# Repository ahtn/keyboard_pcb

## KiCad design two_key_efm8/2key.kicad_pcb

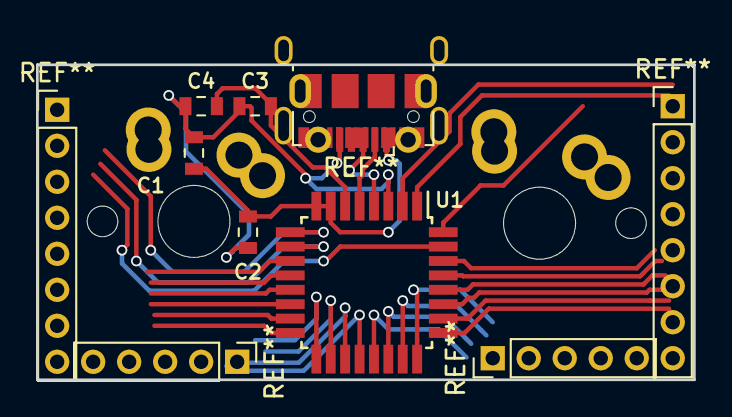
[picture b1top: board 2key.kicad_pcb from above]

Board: 2 copper layers, 36.5 x 17.5 mm, 8 parts (0 on the bottom side), 5 nets.

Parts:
C1, C2, C3, C4: C; C_0603_1608Metric
J1: USB_OTG; USB_Micro-B_Molex-105017-0001
K1_1, K1_1#2: SW_PUSH; Cherry_MX_Matias_No_Silk_Border
U1: EFM8UB2_32; TQFP-32_7x7mm_P0.8mm

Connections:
+3V3: C3.1, C4.1, U1.6
GND: C1.2, C2.2, C3.2, C4.2, J1.5, U1.3
unnamed: C1.1, C2.1, J1.1, U1.7, U1.8
unnamed: J1.2, U1.5
unnamed: J1.3, U1.4

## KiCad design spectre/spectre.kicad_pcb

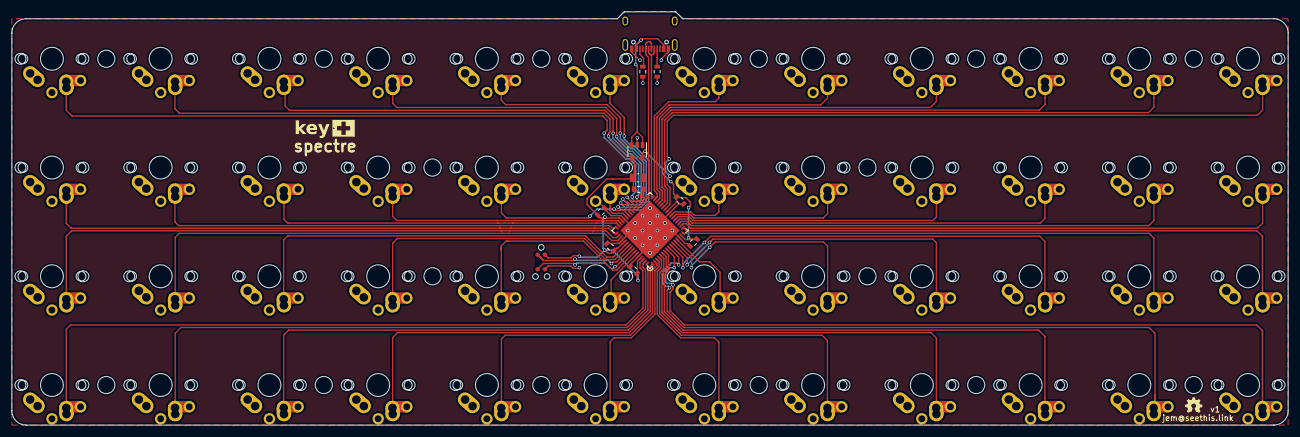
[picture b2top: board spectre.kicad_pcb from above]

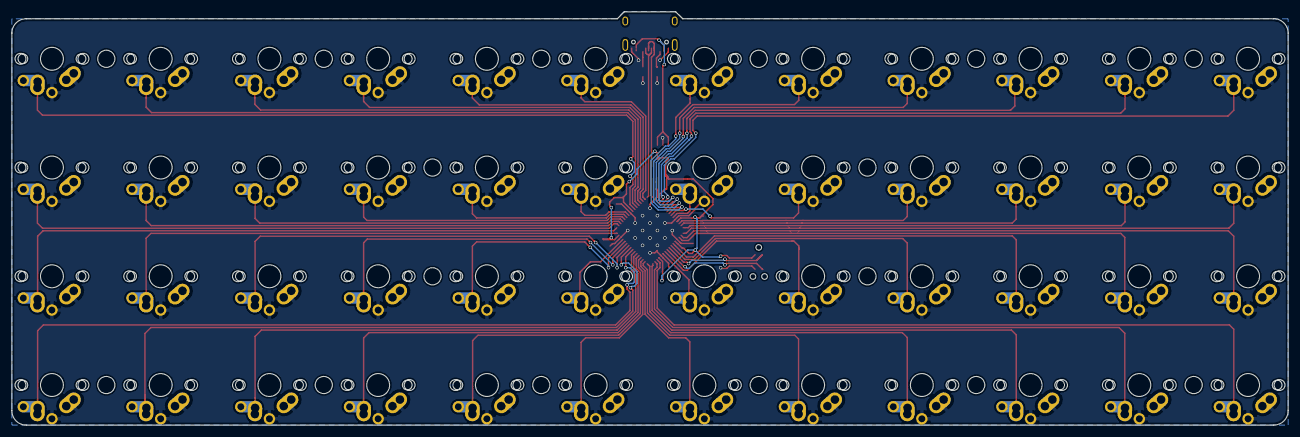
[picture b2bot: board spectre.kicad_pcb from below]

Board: 2 copper layers, 223.0 x 72.2 mm, 61 parts (48 on the bottom side), 57 nets.

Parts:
C1: 10uF; C_0805_2012Metric
C2, C3, C4, C5, C6, C7: 0.1uF; C_0603_1608Metric
J1: TC2030-IDC; TC2030-NL_SMALL
J2: USB_Type_C_2.0_Receptacle; USB_TypeC_U31F-24SNA0201
K0, K1, K2, K3, K4, K5, K6, K7, K8, K9, K10, K11, K12, K13, K14, K15, K16, K17, K18, K19, K20, K21, K22, K23, K24, K25, K26, K27, K28, K29, K30, K31, K32, K33, K34, K35, K36, K37, K38, K39, K40, K41, K42, K43, K44, K45, K46, K47: K00; Cherry_MX_Matias_KailhLP_NoSilk
R1, R2: R; R_0603_1608Metric
U1: MIC550X; SOT-23-5
U2: ATXMEGA64A3U-MH; QFN-64-1EP_9x9mm_P0.5mm

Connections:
+5V: J2.A4, J2.B4, U1.1, U1.3
/D+: J2.A6, J2.B6, U2.33
/D-: J2.A7, J2.B7, U2.32
/KEY0: K0.2, U2.37
/KEY1: K1.2, U2.36
/KEY2: K2.2, U2.38
/KEY3: K3.2, U2.39
/KEY4: K4.2, U2.40
/KEY5: K5.2, U2.41
/KEY6: K6.2, U2.31
/KEY7: K7.2, U2.30
/KEY8: K8.2, U2.29
/KEY9: K9.2, U2.28
/KEY10: K10.2, U2.27
/KEY11: K11.2, U2.26
/KEY12: K12.2, U2.49
/KEY13: K13.2, U2.48
/KEY14: K14.2, U2.47
/KEY15: K15.2, U2.46
/KEY16: K16.2, U2.42
/KEY17: K17.2, U2.43
/KEY18: K18.2, U2.23
/KEY19: K19.2, U2.22
/KEY20: K20.2, U2.21
/KEY21: K21.2, U2.20
/KEY22: K22.2, U2.19
/KEY23: K23.2, U2.18
/KEY24: K24.2, U2.50
/KEY25: K25.2, U2.51
/KEY26: K26.2, U2.54
/KEY27: K27.2, U2.55
/KEY28: K28.2, U2.58
/KEY29: K29.2, U2.59
/KEY30: K30.2, U2.13
/KEY31: K31.2, U2.12
/KEY32: K32.2, U2.11
/KEY33: K33.2, U2.10
/KEY34: K34.2, U2.16
/KEY35: K35.2, U2.17
/KEY36: K36.2, U2.62
/KEY37: K37.2, U2.63
/KEY38: K38.2, U2.64
/KEY39: K39.2, U2.1
/KEY40: K40.2, U2.2
/KEY41: K41.2, U2.3
/KEY42: K42.2, U2.4
/KEY43: K43.2, U2.5
/KEY44: K44.2, U2.6
/KEY45: K45.2, U2.7
/KEY46: K46.2, U2.9
/KEY47: K47.2, U2.8
/PDI: J1.1, U2.56
/RST: J1.5, U2.57
GND: C1.1, C2.1, C3.1, C4.1, C5.1, C6.1, C7.1, J1.6, J2.A1, J2.B1, K0.1, K1.1, K2.1, K3.1, K4.1, K5.1, K6.1, K7.1, K8.1, K9.1, K10.1, K11.1, K12.1, K13.1, K14.1, K15.1, K16.1, K17.1, K18.1, K19.1, K20.1, K21.1, K22.1, K23.1, K24.1, K25.1, K26.1, K27.1, K28.1, K29.1, K30.1, K31.1, K32.1, K33.1, K34.1, K35.1, K36.1, K37.1, K38.1, K39.1, K40.1, K41.1, K42.1, K43.1, K44.1, K45.1, K46.1, K47.1, R1.2, R2.2, U1.2, U2.14, U2.24, U2.34, U2.44, U2.52, U2.60, U2.65
unnamed: J2.A5, R2.1
unnamed: J2.B5, R1.1
VCC: C1.2, C2.2, C3.2, C4.2, C5.2, C6.2, C7.2, J1.2, U1.4, U1.5, U2.15, U2.25, U2.35, U2.45, U2.53, U2.61

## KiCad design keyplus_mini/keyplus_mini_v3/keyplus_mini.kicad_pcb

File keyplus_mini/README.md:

# keyplus mini beta

## Errata rev2

The SS and MO pins are mislabeled. The SS pin should be MO, and the MO pin
should be SS.

## Wiring

### Wiring key matrix

The key matrix should be wired to the ROW and COL pins on the PCB. Wiring of the
ROW and COL pins should start from the lowest number pin (i.e. `ROW0`
and `COL0`) and work up in consecutive order. The diodes in the key matrix should
point from the COL to ROW pins (other scan modes not implemented yet).

The `COL15, COL14, COL13, COL12` pins (underlined on the PCB) may also be used
as `ROW` pins. They map to the following row pins:

* ROW6: COL15
* ROW7: COL14
* ROW8: COL13
* ROW9: COL12

Thus it is possible to have up to 120 keys connected using a 10x12 matrix.

### Wired split with I2C

To connect to boards with I2C for wired split, connect the 5V, SDA, SCL, and
GND pins between devices. You can connect several devices in this manner. They
just need to share 5V, SDA, SCL and GND pins.

I would recommend **NOT** using TRRS connectors for wired split. While
connecting and disconnecting the cabel, the contacts inside the TRRS cable can
short to one another. Instead, I would recommend using micro USB ports, or
another connector that doesn't short it's contacts when it is
plugged/unplugged. Then you will be able to take advantage of the
wireless/wired hot plugging functionality without worrying about damaging the
hardware.  You can find male-to-male micro USB cables online with a bit of
searching.

### Wireless with nRF24L01+

To use wireless mode, you will need a battery and a nRF24L01+ module. The
battery should be 3V. Some options for the battery are 1xCR2032, 2xAA/AAA, or
1xAA/AAA with a boost converter. Note the keyplus mini controller does not
support any sort of charging of the batteries. When there is no USB connecting
the device will run off battery power. When the USB is plugged in, it will
automatically switch to run off USB power. To connect the battery connect:

* BAT -> positive battery terminal
* GND -> negative battery terminal

To connect an nRF24L01+ module you will need to connect these pins:

* xmega -> nRF24L01+
* R0 -> CE
* R1  -> IRQ
* MO -> MO / MOSI  (Note: rev2 PCB use SS instead)
* MI -> MI / MISO
* SS -> SS / CSN (Note: rev2 PCB use MO instead)
* SCK -> SCK
* GND -> GND
* 3V -> 3.3V

Note: currently the IRQ pin is not used in the code, but I'll add code to take advantage of it soon.

### PCB schematic for rev 2

[Schematic for keyplus mini](https://rawgit.com/ahtn/keyboard_pcb/bb20b354216aa1858254db9946aa67aa8df67bfd/keyplus_mini/rev2/keyplus_mini.pdf)

### Mechanical information for rev 2

## Layout file format and programming

TODO

For [prebuilt versions of the loader and firmware](https://github.com/ahtn/keyplus/releases).

For the mean time, refer to the
[example layouts](https://github.com/ahtn/keyplus/tree/master/layouts), and the
[list of available keycodes](https://github.com/ahtn/keyplus/blob/master/host-software/layout/mapped_keycodes.py#L8).

## Current firmware limitations

Firmware is still in beta and several features are not completely
finished yet. Some prominent ones:

* Macro and hold keycodes can't be used in the layout config file yet.
* No LED support yet (including indicators)
* Pairing Unifying mouse is not exposed to devices yet

## Testing key matrix

The firmware supports a mode where it will pass the raw keyboard matrix data to
the PC. This can be used to check the row and column pairs in your key matrix.
Currently, this can only be used on the command line using a python script
[`keyplus/host-software/keyplus_cli.py`](https://github.com/ahtn/keyplus/blob/master/host-software/keyplus_cli.py).

To use the keyboard matrix passthrough mode, run `./keyplus_cli.py passthrough`
and you should see output like this:

```
$$ ./keyplus_cli.py passthrough
r3c5

r3c0

r1c0

r0c1
r0c1 r1c1
r1c1
r1c1 r3c3
r3c3
```

Where each line shows which keys in the matrix are currently being pressed.
Note only devices directly connected by USB will report key presses using
passthrough mode.

## Unifying flasher

First working version of the Unifying flashing script can be
[found here](https://github.com/ahtn/keyplus/tree/master/host-software/uniflash).
Currently this script has only been tested on Linux.

There are two types of Unifying receivers that use different microcontrollers:
nRF24LU1+ and CC2544.
Only Unifying receivers that use the nRF24LU1+ are supported.

You can check which kind you have by looking at the firmware version number
of the receiver in Logitech's Unifying Software (or Solaar on Linux). If your
receiver has a firmware number that starts with 12 (e.g. `012.005.00028`), then
it uses the nRF24LU1+. If it starts with 24, then it uses the CC2544.

You can find Unifying receivers on aliexpress. I've tried a few different types
and they have all used the nRF24LU1+.

### How to add dongle to layout file

To be able to use the dongle, you need to add it to your layout file:

```yaml
devices:
  nrf_dongle:
    id: 7       # unique id that is not used by any of your other devices
    scan_mode: # rf dongle, so don't need a matrix
      mode: no_matrix # options: col_row, pins, no_matrix
```

Then you need to load the layout file and RF configuration file to the device.

## xusb bootloader

The bootloader installed on the ATxmega is the [xusb bootloader](https://github.com/ahtn/xusb-boot).
To enter bootloader mode press the reset button (or short the RST and GND
contacts) once when the USB cable is plugged in. The device will remain in
bootloader mode until it is programmed, or until the reset button is pressed a
second time.  For a more detailed explanation of the bootloader, [see
here](https://github.com/ahtn/xusb-boot#ways-to-enter-the-bootloader).

The lock bits on the ATxmega have been set to disable reading from flash by an
external programmer. This is done to protect the encryption keys that are
stored in flash.  Also, for security reasons the bootloader will wipe SRAM on
power up.

## Trouble shooting and known issues

* Make sure that the battery contacts have a firm connection. I've had issues
  sometimes with my homemade CR2032 holders where vibrations from typing would
  cause the contacts to be unreliable.
* When using the xmega+nRF24L01+ as the wireless receiver, it will sometimes
  drop packets [due to this issue](https://github.com/ahtn/keyplus/issues/3).
  Should be fixed soon. The nRF24LU1+ implementation doesn't have this problem.
* If you load broken firmware onto the xmega, it won't be visible to the GUI
  loader or flashing scripts. In this case you will need to enter it's bootloader
  manually by shorting the RST pin to GND while it is connected via USB. The
  bootloader is stored in a protected region of flash, so the bootloader should
  be unbrickable.
* Currently if you have multiple devices acting as wireless receivers at the
  same time, they will interfere with each other. This will be fixed later.

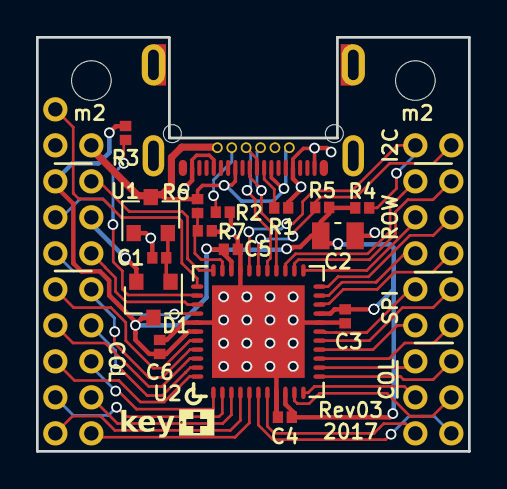
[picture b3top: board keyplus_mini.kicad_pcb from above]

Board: 2 copper layers, 24.0 x 23.0 mm, 20 parts (0 on the bottom side), 43 nets.

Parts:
C1: 1uF; C_0402_1005Metric
C2: 10uF; C_0805_2012Metric
C3, C4, C5, C6: 0.1uF; C_0402_1005Metric
D1: D_Schottky_x2_KCom_AAK; SOT-23
J1: USB_C_Receptacle; USB_TypeC_Hirose_CX70M-24P1
J2, J4: Conn_02x09_Odd_Even; PinHeader_2x09_P2.00mm_Vertical
J3: CONN_01X01; PinHeader_1x01_P2.00mm_Vertical
R1, R2: 5.1k; R_0402_1005Metric
R3, R4, R5: 10k; R_0402_1005Metric
R6, R7: 100k; R_0402_1005Metric
U1: MCP1700-3302E_SOT23; SOT-23
U2: ATXMEGA-A4U-EPAD; QFN-44-1EP_7x7mm_Pitch0.5mm

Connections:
+3V3: C2.2, C3.2, C4.2, C5.2, C6.2, D1.3, J2.3, R3.1, R4.1, R5.1, U2.9, U2.19, U2.31, U2.39
+5V: J1.A4, J1.A9, J1.B4, J1.B9, J2.2, R6.1, U1.3
+BATT: D1.2, J2.6
/D+: J1.A6, J1.B6, U2.27
/D-: J1.A7, J1.B7, U2.26
/PA0: J2.9, U2.40
/PA1: J2.10, U2.41
/PA2: J2.11, U2.42
/PA3: J2.12, U2.43
/PA4: J2.13, U2.44
/PA5: J2.14, U2.1
/PA6: J2.15, U2.2
/PA7: J2.16, U2.3
/PB0: J2.17, U2.4
/PB1: J2.18, U2.5
/PB2: J4.18, U2.6
/PB3: J4.17, U2.7
/PC0: J4.16, U2.10
/PC1: J4.15, U2.11
/PC2: J4.14, U2.12
/PC3: J4.13, U2.13
/PC4: J4.12, U2.14
/PC5: J4.11, U2.15
/PC6: J4.10, U2.16
/PC7: J4.9, U2.17
/PCL: J2.5, R3.2, U2.35
/PD0: J4.8, U2.20
/PD1: J4.7, U2.21
/PD2: J4.6, U2.22
/PD3: J4.5, U2.23
/PD4: J4.4, U2.24
/PD5: J4.3, U2.25
/PDI: J3.1, U2.34
/PE0: J4.2, R5.2, U2.28
/PE1: J4.1, R4.2, U2.29
/PE3: J2.4, U2.33
/PR0: J2.8, U2.36
/PR1: J2.7, U2.37
GND: C1.1, C2.1, C3.1, C4.1, C5.1, C6.1, J1.A1, J1.A12, J1.B1, J1.B12, J2.1, R1.2, R2.2, R7.2, U1.1, U2.8, U2.18, U2.30, U2.38, U2.45
unnamed: C1.2, D1.1, U1.2
unnamed: J1.A5, R1.1
unnamed: J1.B5, R2.1
unnamed: R6.2, R7.1, U2.32

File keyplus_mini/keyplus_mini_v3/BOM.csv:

Designator,Part,Value,Quantity,Digi-key Part Number,,Datasheet
"R1, R2",,5.1k,2,311-5.10KLRCT-ND ,,
"R3, R4, R5",,10k,3,311-10KJRCT-ND ,,
"R6, R7",,100k,2,311-100KLRCT-ND ,,
C1,,1uF,1,490-12701-2-ND,,
C2,,10uF,1,490-6473-1-ND,,http://psearch.en.murata.com/capacitor/product/GRM21BR61C106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
"C3, C4, C5, C6",,0.1uF,4,490-6322-2-ND,,
D1,BAT54C,Common cathode diode array,1,BAT54C-FDITR-ND,,https://www.diodes.com/assets/Datasheets/ds11005.pdf
U1,MCP1700T3302,3.3V regulator,1,MCP1700T3302ETTTR-ND,,http://ww1.microchip.com/downloads/en/DeviceDoc/20001826D.pdf
U2,ATXMEGA32A4U-MH,ATXMEGA mcu,1,ATXMEGA32A4U-MH-ND,,http://www.atmel.com/images/Atmel-8387-8-and16-bit-AVR-Micro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
J1,CX70M-24P1 ,USB Type-C Receptacle,1,H125292CT-ND,,https://www.hirose.com/product/en/download_file/key_name/CX7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
"J2, J3, J4",DNP,DNP,,,,

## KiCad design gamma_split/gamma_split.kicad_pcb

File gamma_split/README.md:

# γ-split (prototype)

## License

[CC-BY-NC](https://creativecommons.org/licenses/by-nc/4.0/)

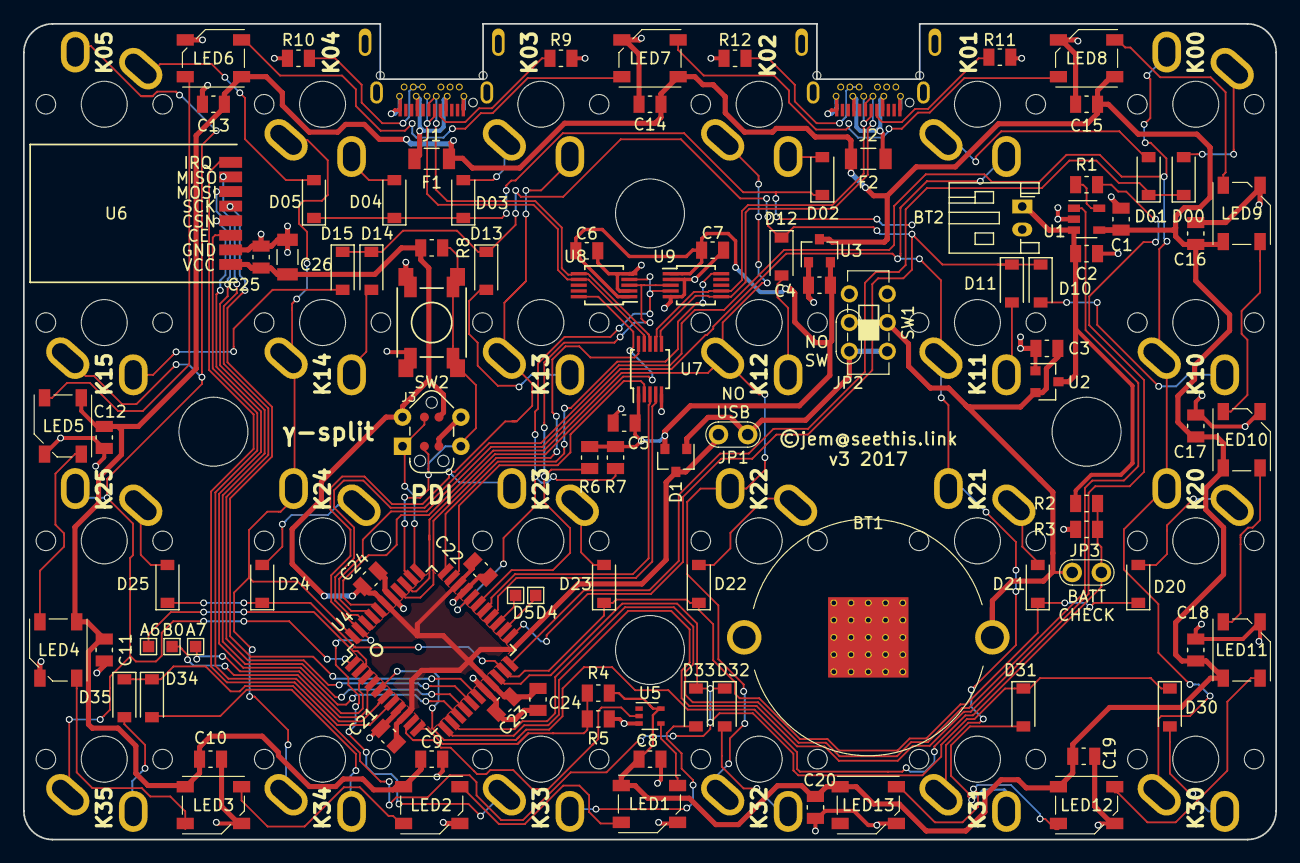
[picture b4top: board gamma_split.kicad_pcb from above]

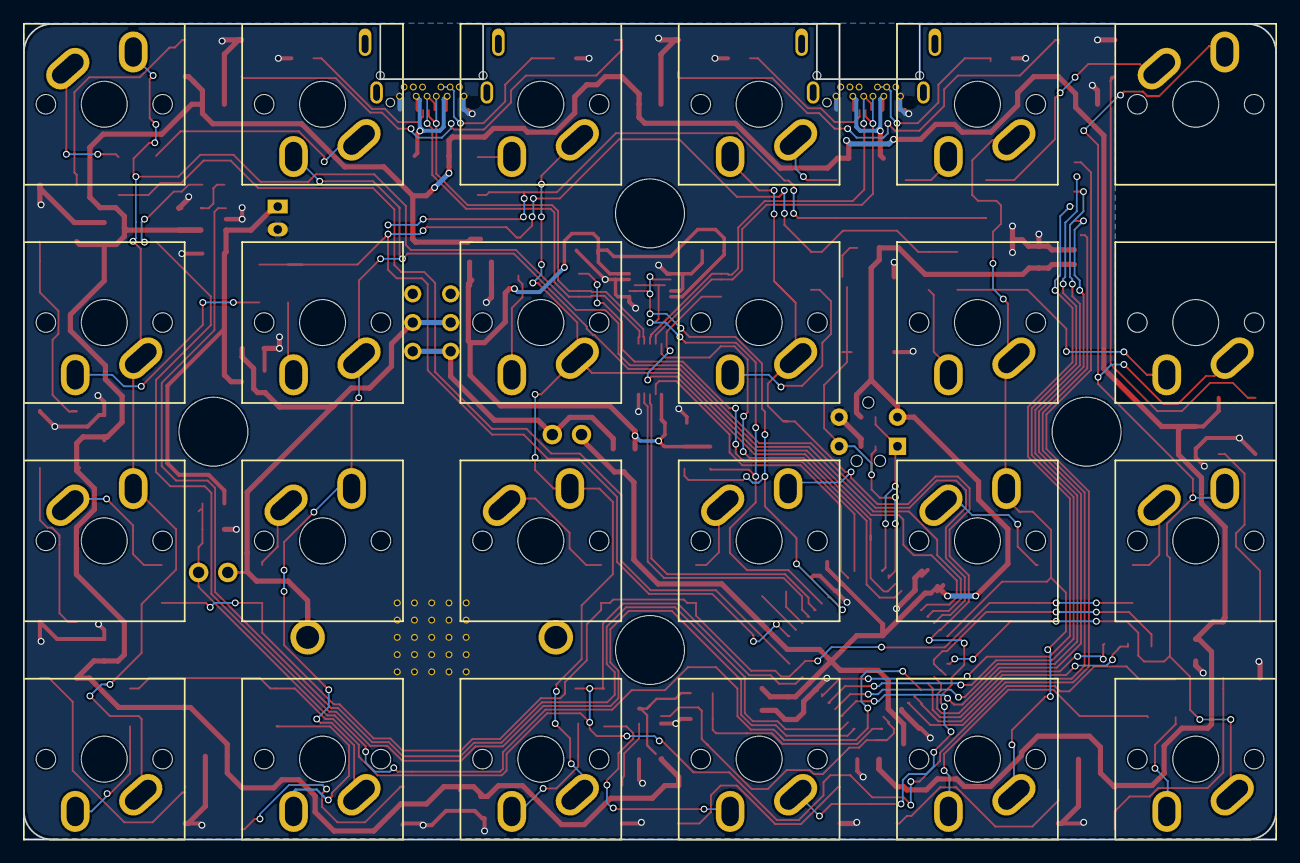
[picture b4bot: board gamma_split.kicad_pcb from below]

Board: 2 copper layers, 109.0 x 71.0 mm, 127 parts (24 on the bottom side), 91 nets.

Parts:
BT1: Battery; CR2032_MPD_BK-913_NoSolderMask
BT2: Battery_Cell; JST_PH_S2B-PH-K_1x02_P2.00mm_Horizontal
C1, C2: 4.7uF; C_0805_2012Metric
C3, C4: 1uF; C_0805_2012Metric
C5, C6, C7, C8, C9, C10, C11, C12, C13, C14, C15, C16, C17, C18, C19, C20, C21, C22, C23, C24, C24#2: 0.1uF; C_0805_2012Metric
C25: 10uF; C_0805_2012Metric
C26: 47uF; C_1206_3216Metric
D00, D01, D02, D03, D04, D05, D10, D11, D12, D13, D14, D15, D20, D21, D22, D23, D24, D25, D30, D31, D32, D33, D34, D35: D; D_SOD-123
D1: D_Schottky_x2_KCom_AAK; SOT-23
F1, F2: Fuse; R_1206_3216Metric
J1, J2: USB_C_Receptacle; USB_TypeC_DX07B024XJ1
J3: TC2030-IDC; TC2030-NL_SMALL_AND_IDC_PDI
J4: D4; TestPoint_Pad_1.0x1.0mm
J5: D5; TestPoint_Pad_1.0x1.0mm
J6: A6; TestPoint_Pad_1.0x1.0mm
J7: A7; TestPoint_Pad_1.0x1.0mm
J8: B0; TestPoint_Pad_1.0x1.0mm
JP1: NO USB; Jumper_1x02_P2.54mm_THT
JP2: NO SW; Jumper_1x02_P2.54mm_THT
JP3: BATT CHECK; Jumper_1x02_P2.54mm_THT
K00: K00; Cherry_MX_Matias_Slots_NoSilk_Back
K01: K01; Cherry_MX_Matias_Slots_NoSilk_Back
K02: K02; Cherry_MX_Matias_Slots_NoSilk_Back
K03: K03; Cherry_MX_Matias_Slots_NoSilk_Back
K04: K04; Cherry_MX_Matias_Slots_NoSilk_Back
K05: K05; Cherry_MX_Matias_Slots_NoSilk_Back
K10: K10; Cherry_MX_Matias_Slots_NoSilk_Back
K11: K11; Cherry_MX_Matias_Slots_NoSilk_Back
K12: K12; Cherry_MX_Matias_Slots_NoSilk_Back
K13: K13; Cherry_MX_Matias_Slots_NoSilk_Back
K14: K14; Cherry_MX_Matias_Slots_NoSilk_Back
K15: K15; Cherry_MX_Matias_Slots_NoSilk_Back
K20: K20; Cherry_MX_Matias_Slots_NoSilk_Back
K21: K21; Cherry_MX_Matias_Slots_NoSilk_Back
K22: K22; Cherry_MX_Matias_Slots_NoSilk_Back
K23: K23; Cherry_MX_Matias_Slots_NoSilk_Back
K24: K24; Cherry_MX_Matias_Slots_NoSilk_Back
K25: K25; Cherry_MX_Matias_Slots_NoSilk_Back
K30: K30; Cherry_MX_Matias_Slots_NoSilk_Back
K31: K31; Cherry_MX_Matias_Slots_NoSilk_Back
K32: K32; Cherry_MX_Matias_Slots_NoSilk_Back
K33: K33; Cherry_MX_Matias_Slots_NoSilk_Back
K34: K34; Cherry_MX_Matias_Slots_NoSilk_Back
K35: K35; Cherry_MX_Matias_Slots_NoSilk_Back
LED1, LED2, LED3, LED4, LED5, LED6, LED7, LED8, LED9, LED10, LED11, LED12, LED13: WS2812B
R1, R6, R7, R8: 10k; R_0805_2012Metric
R2, R3: 470k; R_0805_2012Metric
R4, R5: 100k; R_0805_2012Metric
R9, R10, R11, R12: 5.1k; R_0805_2012Metric
SW1: Switch-6P-2S2T; SlideSwitch_C&K_JS202011CQN
SW2: SW_Push; SwitchPush_C&K_MultiFoot_RS-187R05A2-DS_And_PTS645_SMT
U1: MCP73831; SOT-23-5
U2: MCP1700 (3.0V); SOT-23
U3: MCP1700 (3.3V); SOT-23
U4: ATXMEGA-A4U-EPAD; TQFP-44_10x10mm_P0.8mm
U5: 74LVC1G34; SOT-353_SC-70-5
U6: nRF24L01_module; NRF24L01-Module-SMD
U7, U8, U9: FSUSB42; MSOP-10_3x3mm_P0.5mm

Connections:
+3V3: C4.2, C5.1, C6.1, C7.1, D1.2, R6.1, R7.1, U3.2, U7.1, U8.1, U9.1
+5V: C1.1, C8.1, C9.1, C10.1, C11.1, C12.1, C13.1, C14.1, C15.1, C16.1, C17.1, C18.1, C19.1, C20.1, F1.2, F2.2, LED1.1, LED2.1, LED3.1, LED4.1, LED5.1, LED6.1, LED7.1, LED8.1, LED9.1, LED10.1, LED11.1, LED12.1, LED13.1, R4.1, U1.4, U3.3, U5.5
+BATT: D1.1, JP1.1, SW1.1, SW1.4
/A6: J6.1, U4.2
/A7: J7.1, U4.3
/B0: J8.1, U4.4
/BATT_IN: BT1.1, C3.2, JP3.1, SW1.2, SW1.5, U2.2
/BAT_LI_ION: BT2.1, C2.1, R2.1, U1.3, U2.3
/BAT_LVL: JP3.2, R2.2, R3.1, U4.5
/BAT_PROG: R1.2, U4.12
/BAT_STAT: U1.1, U4.13
/CE: U4.6, U6.3
/COL0: K00.2, K10.1, K20.2, K30.1, U4.42
/COL1: K01.2, K11.1, K21.2, K31.1, U4.41
/COL2: K02.1, K12.1, K22.2, K32.1, U4.40
/COL3: K03.2, K13.1, K23.2, K33.1, U4.43
/COL4: K04.1, K14.1, K24.2, K34.1, U4.44
/COL5: K05.2, K15.1, K25.2, K35.1, U4.1
/CSN: U4.14, U6.4
/D4: J4.1, U4.24
/D5: J5.1, U4.25
/D+: U4.27, U7.3
/D-: U4.26, U7.4
/I2C_LEFT: U4.36, U8.10
/I2C_RIGHT: U4.33, U9.10
/IRQ: U4.7, U6.8
/MISO: U4.16, U6.7
/MOSI: U4.15, U6.6
/PDI: J3.1, U4.34
/ROW0: D00.1, D01.1, D02.1, D03.1, D04.1, D05.1, U4.22
/ROW1: D10.1, D11.1, D12.1, D13.1, D14.1, D15.1, U4.23
/ROW2: D20.1, D21.1, D22.1, D23.1, D24.1, D25.1, U4.21
/ROW3: D30.1, D31.1, D32.1, D33.1, D34.1, D35.1, U4.20
/RST: J3.5, R8.2, SW2.2, U4.35
/SCK: U4.17, U6.5
/SCL: R7.2, U4.29, U8.4, U9.4
/SDA: R6.2, U4.28, U8.3, U9.3
/UNDER_LED: U4.10, U5.2
/USB_L_D+: J1.A6, J1.B6, U7.9, U8.7
/USB_L_D-: J1.A7, J1.B7, U7.8, U8.6
/USB_OE: U4.37, U7.10
/USB_R_D+: J2.A6, J2.B6, U7.7, U9.7
/USB_R_D-: J2.A7, J2.B7, U7.6, U9.6
/USB_SEL: U4.32, U7.2
/VBUS_CHECK: R4.2, R5.1, U4.11
GND: BT1.2, BT2.2, C1.2, C2.2, C3.1, C4.1, C5.2, C6.2, C7.2, C8.2, C9.2, C10.2, C11.2, C12.2, C13.2, C14.2, C15.2, C16.2, C17.2, C18.2, C19.2, C20.2, C21.1, C22.1, C23.1, C24.1, C24#2.1, C25.1, C26.1, J1.A1, J1.A12, J1.B1, J1.B12, J2.A1, J2.A12, J2.B1, J2.B12, J3.6, LED1.3, LED2.3, LED3.3, LED4.3, LED5.3, LED6.3, LED7.3, LED8.3, LED9.3, LED10.3, LED11.3, LED12.3, LED13.3, R3.2, R5.2, R9.2, R10.2, R11.2, R12.2, SW2.1, U1.2, U2.1, U3.1, U4.8, U4.18, U4.30, U4.38, U5.3, U6.2, U7.5, U8.2, U8.5, U9.2, U9.5
unnamed: D00.2, K00.1
unnamed: D01.2, K01.1
unnamed: D02.2, K02.2
unnamed: D03.2, K03.1
unnamed: D04.2, K04.2
unnamed: D05.2, K05.1
unnamed: D10.2, K10.2
unnamed: D11.2, K11.2
unnamed: D12.2, K12.2
unnamed: D13.2, K13.2
unnamed: D14.2, K14.2
unnamed: D15.2, K15.2
unnamed: D20.2, K20.1
unnamed: D21.2, K21.1
unnamed: D22.2, K22.1
unnamed: D23.2, K23.1
unnamed: D24.2, K24.1
unnamed: D25.2, K25.1
unnamed: D30.2, K30.2
unnamed: D31.2, K31.2
unnamed: D32.2, K32.2
unnamed: D33.2, K33.2
unnamed: D34.2, K34.2
unnamed: D35.2, K35.2
unnamed: F1.1, J1.A4, J1.A9, J1.B4, J1.B9
unnamed: F2.1, J2.A4, J2.A9, J2.B4, J2.B9
unnamed: J1.A5, R9.1
unnamed: J1.B3, J1.B5, R10.1
unnamed: J2.A5, R11.1
unnamed: J2.B3, J2.B5, R12.1
unnamed: LED1.2, LED2.4
unnamed: LED1.4, U5.4
unnamed: LED2.2, LED3.4
unnamed: LED3.2, LED4.4
unnamed: LED4.2, LED5.4
unnamed: LED5.2, LED6.4
unnamed: LED6.2, LED7.4
unnamed: LED7.2, LED8.4
unnamed: LED8.2, LED9.4
unnamed: LED10.2, LED11.4
unnamed: LED9.2, LED10.4
unnamed: LED11.2, LED12.4
unnamed: LED12.2, LED13.4
unnamed: R1.1, U1.5
VCC: C21.2, C22.2, C23.2, C24.2, C24#2.2, C25.2, C26.2, D1.3, J3.2, JP1.2, R8.1, U4.9, U4.19, U4.31, U4.39, U6.1

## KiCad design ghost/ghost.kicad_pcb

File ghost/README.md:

# keyplus ghost

Minimal component, 3x10 grid keyboard

## License

[CC-BY-SA](https://creativecommons.org/licenses/by-sa/4.0/)

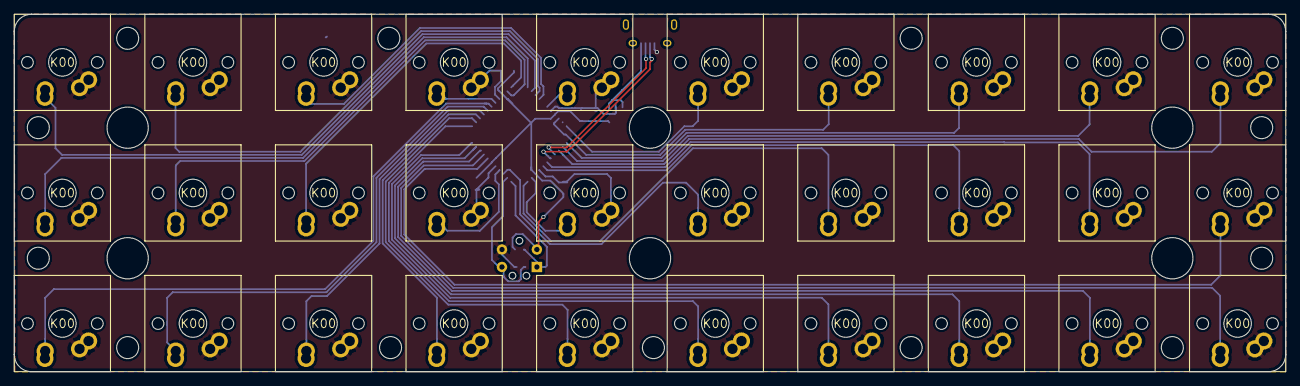
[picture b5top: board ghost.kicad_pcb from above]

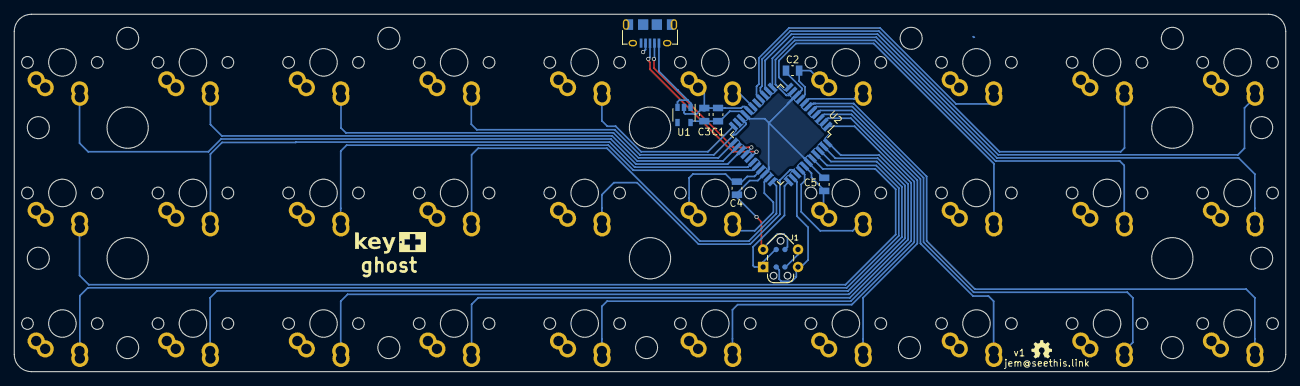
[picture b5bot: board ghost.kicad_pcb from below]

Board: 2 copper layers, 185.0 x 52.0 mm, 39 parts (9 on the bottom side), 37 nets.

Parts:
C1: 10uF; C_0805_2012Metric
C2, C3, C4, C5: 0.1uF; C_0805_2012Metric
J1: TC2030-IDC; TC2030-NL_SMALL_AND_IDC_PDI
J2: USB_B; USB_MicroB_Amphenol_10118194-0001LF
K0, K1, K2, K3, K4, K5, K6, K7, K8, K9, K10, K11, K12, K13, K14, K15, K16, K17, K18, K19, K20, K21, K22, K23, K24, K25, K26, K27, K28, K29: K00; Cherry_MX_Matias_NoSilk.B
U1: MIC550X; SOT-23-5
U2: ATXMEGA-A4U-EPAD; TQFP-44_10x10mm_P0.8mm

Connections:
+5V: J2.1, U1.1, U1.3
/D+: J2.3, U2.27
/D-: J2.2, U2.26
/KEY0: K0.2, U2.13
/KEY1: K1.2, U2.14
/KEY2: K2.2, U2.15
/KEY3: K3.2, U2.7
/KEY4: K4.2, U2.17
/KEY5: K5.2, U2.22
/KEY6: K6.2, U2.20
/KEY7: K7.2, U2.23
/KEY8: K8.2, U2.24
/KEY9: K9.2, U2.25
/KEY10: K10.2, U2.12
/KEY11: K11.2, U2.10
/KEY12: K12.2, U2.11
/KEY13: K13.2, U2.37
/KEY14: K14.2, U2.32
/KEY15: K15.2, U2.36
/KEY16: K16.2, U2.33
/KEY17: K17.2, U2.29
/KEY18: K18.2, U2.28
/KEY19: K19.2, U2.40
/KEY20: K20.2, U2.6
/KEY21: K21.2, U2.5
/KEY22: K22.2, U2.4
/KEY23: K23.2, U2.3
/KEY24: K24.2, U2.2
/KEY25: K25.2, U2.1
/KEY26: K26.2, U2.44
/KEY27: K27.2, U2.43
/KEY28: K28.2, U2.42
/KEY29: K29.2, U2.41
/PDI: J1.1, U2.34
/RST: J1.5, U2.35
GND: C1.1, C2.1, C3.1, C4.1, C5.1, J1.6, J2.4, K0.1, K1.1, K2.1, K3.1, K4.1, K5.1, K6.1, K7.1, K8.1, K9.1, K10.1, K11.1, K12.1, K13.1, K14.1, K15.1, K16.1, K17.1, K18.1, K19.1, K20.1, K21.1, K22.1, K23.1, K24.1, K25.1, K26.1, K27.1, K28.1, K29.1, U1.2, U2.8, U2.18, U2.30, U2.38
VCC: C1.2, C2.2, C3.2, C4.2, C5.2, J1.2, U1.5, U2.9, U2.19, U2.31, U2.39

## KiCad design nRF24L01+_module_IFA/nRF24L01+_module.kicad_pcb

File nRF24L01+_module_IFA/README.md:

# nRF24L01+ module with IFA

## License

[CC-BY-SA](https://creativecommons.org/licenses/by-sa/4.0/)

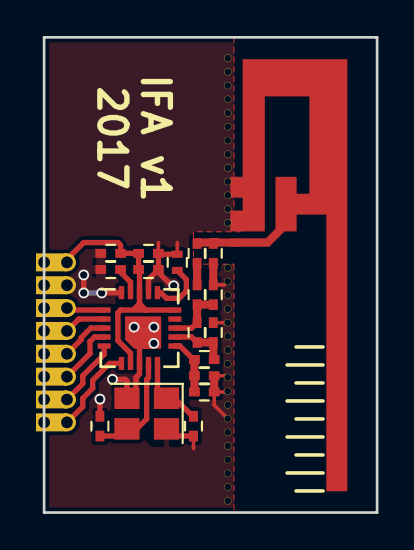
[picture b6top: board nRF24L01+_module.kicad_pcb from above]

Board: 2 copper layers, 18.5 x 26.4 mm, 20 parts (0 on the bottom side), 17 nets.

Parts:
ANT1: 50ohm; f_inverted_antenna
C1, C2: 22pF; C_0402
C3: 2.2nF; C_0402
C4: 4.7pF; C_0402
C5: 1.5pF; C_0402
C6: 1.0pF; C_0402
C7: 33nF; C_0402
C8: 1nF; C_0402
C9: 10nF; C_0402
C10, C12: C; C_0402
C11: 4.7uF; C_0402
J1: Conn_01x08; Pin_Header_Castellated_1x08_Pitch1.27mm_no_silk
L1: 8.2nH; C_0402
L2: 2.7nH; C_0402
L3: 3.9nH; C_0402
R2: 22k; R_0402
U1: nRF24L01+; QFN-20-1EP_4x4mm_Pitch0.5mm
X1: 16MHz; Crystal_SMD_3225-4pin_3.2x2.5mm

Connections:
/CE: J1.3, U1.1
/CSN: J1.4, U1.2
/IRQ: J1.8, U1.6
/MISO: J1.7, U1.5
/MOSI: J1.6, U1.4
/SCK: J1.5, U1.3
unnamed: ANT1.1, C5.1, C6.1
unnamed: C1.1, U1.10, X1.1
unnamed: C2.1, U1.9, X1.3
unnamed: C3.1, C4.1, L2.1, U1.11
unnamed: C5.2, L3.1
unnamed: C7.1, U1.19
unnamed: C10.1, L1.2, L3.2, U1.13
unnamed: C12.1, L1.1, L2.2, U1.12
unnamed: R2.2, U1.16
VDD: C8.1, C9.1, C11.1, J1.1, U1.7, U1.15, U1.18
VSS: ANT1.2, C1.2, C2.2, C3.2, C4.2, C6.2, C7.2, C8.2, C9.2, C10.2, C11.2, C12.2, J1.2, R2.1, U1.8, U1.14, U1.17, U1.20, X1.2, X1.4

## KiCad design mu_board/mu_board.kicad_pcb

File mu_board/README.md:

# μ-board PCB

## Firmware

[See here](https://github.com/ahtn/keyplus)

## License

[CC-BY-SA](https://creativecommons.org/licenses/by-sa/4.0/)

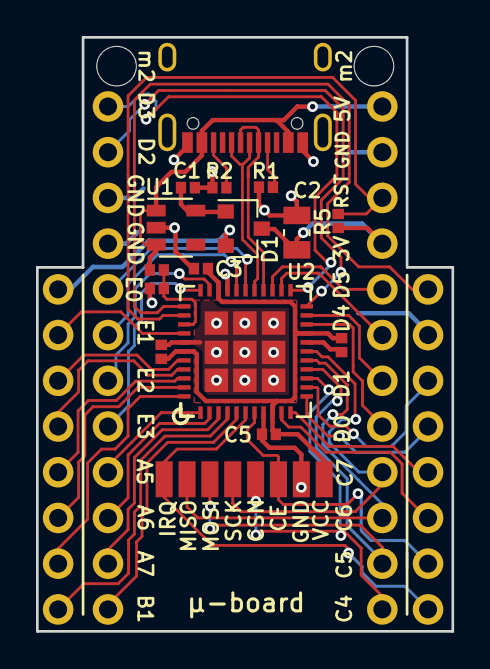
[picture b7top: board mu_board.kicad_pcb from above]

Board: 2 copper layers, 23.1 x 33.0 mm, 21 parts (1 on the bottom side), 43 nets.

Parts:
C1: 1uF; C_0402_1005Metric
C2: 10uF; C_0805_2012Metric
C3, C4, C5, C6: 0.1uF; C_0402_1005Metric
D1: D_Schottky_x2_KCom_AAK; SOT-23
J1: USB_C_Receptacle; USB_TypeC_U31F-24SNA0201
J2: Conn_01x11; PinHeader_1x12_P2.54mm_Vertical
J3: Conn_01x08; PinHeader_1x08_P2.54mm_Vertical
J4: Conn_01x13; PinHeader_1x12_P2.54mm_Vertical
J5: Conn_01x06; PinHeader_1x08_P2.54mm_Vertical
OSHW_Logo: G***; OSHW_3x3mm_SilkS
R1, R2: 5.1k; R_0402_1005Metric
R3, R4: 100k; R_0402_1005Metric
R5: 10k; R_0402_1005Metric
U1: MIC5216-3.3BM5; SOT-23-5
U2: ATXMEGA-A4U-EPAD; QFN-44-1EP_7x7mm_Pitch0.5mm_Alt_Silk
U3: nRF24L01_module; NRF24L01-Module-SMD

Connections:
+3V3: C2.2, C3.2, C4.2, C5.2, C6.2, D1.3, J4.4, R5.1, U2.9, U2.19, U2.31, U2.39, U3.1
+5V: J1.A4, J1.B4, J4.1, R4.1, U1.1, U1.3
+BATT: D1.2, J3.1
/D+: J1.A6, J1.B6, U2.27
/D-: J1.A7, J1.B7, U2.26
/PA0: J3.3, U2.40
/PA1: J3.4, U2.41
/PA2: J3.5, U2.42
/PA3: J3.6, U2.43
/PA4: J3.7, U2.44
/PA5: J2.9, U2.1
/PA6: J2.10, U2.2
/PA7: J2.11, U2.3
/PB0: J3.8, U2.4
/PB1: J2.12, U2.5
/PB2: J5.8, U2.6, U3.8
/PB3: J5.7, U2.7, U3.3
/PC0: J5.6, U2.10
/PC1: J5.5, U2.11
/PC2: J5.4, U2.12
/PC3: J5.3, U2.13
/PC4: J4.12, U2.14, U3.4
/PC5: J4.11, U2.15, U3.6
/PC6: J4.10, U2.16, U3.7
/PC7: J4.9, U2.17, U3.5
/PCL: J4.3, R5.2, U2.35
/PD0: J4.8, U2.20
/PD1: J4.7, U2.21
/PD2: J2.2, U2.22
/PD3: J2.1, U2.23
/PD4: J4.6, U2.24
/PD5: J4.5, U2.25
/PDI: J5.1, U2.34
/PE0: J2.5, U2.28
/PE1: J2.6, U2.29
/PE2: J2.7, U2.32
/PE3: J2.8, U2.33
/PR1: J3.2, U2.37
GND: C1.1, C2.1, C3.1, C4.1, C5.1, C6.1, J1.A1, J1.B1, J2.3, J2.4, J4.2, J5.2, R1.2, R2.2, R3.2, U1.2, U2.8, U2.18, U2.30, U2.38, U3.2
unnamed: C1.2, D1.1, U1.5
unnamed: J1.A5, R1.1
unnamed: J1.B5, R2.1
unnamed: R3.1, R4.2, U2.36

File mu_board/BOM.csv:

Designator,Part,Value,Quantity,Digi-key Part Number,Datasheet,Source,,,
"R1, R2",,5.1k,2,311-5.10KLRCT-ND ,,,,,
"R3, R4",,100k,2,311-100KLRCT-ND ,,,,,
R5,,10k,3,311-10KJRCT-ND ,,,,,
C1,,1uF,1,490-12701-2-ND,,,,,
C2,,10uF,1,490-6473-1-ND,http://psearch.en.murata.com/capacitor/product/GRM21BR61C106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,,,,
"C3, C4, C5, C6",,0.1uF,4,490-6322-2-ND,,,,,
D1,BAT54C,Common cathode diode array,1,BAT54C-FDITR-ND,https://www.diodes.com/assets/Datasheets/ds11005.pdf,,,,
U1,MIC5245-3.3,3.3V regulator,1,576-2790-1-ND,http://ww1.microchip.com/downloads/en/DeviceDoc/mic5245.pdf,,,,
U2,ATXMEGA32A4U,,1,ATXMEGA32A4U-MH-ND,http://www.atmel.com/images/Atmel-8387-8-and16-bit-AVR-Micro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,,,,
J1,,USB Type-C Receptacle,1,,http://www.dory-tech.com/UploadFiles/2017/0/2017080810353867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,http://www.dory-tech.com/html/113.html,https://www.aliexpress.com/item/New-Type-C-Connector-16-Pin-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,https://www.aliexpress.com/item/2pcs-lot-USB3-1-Type-C-Femal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,https://www.aliexpress.com/item/20pcs-USB-3-1-Type-C-Connect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

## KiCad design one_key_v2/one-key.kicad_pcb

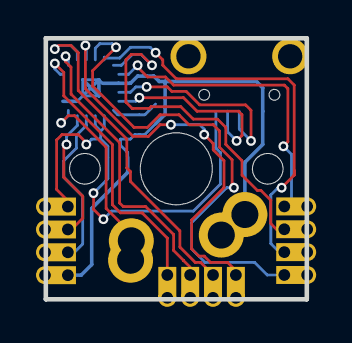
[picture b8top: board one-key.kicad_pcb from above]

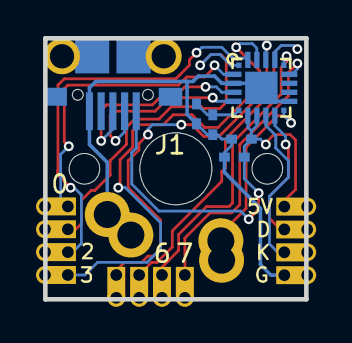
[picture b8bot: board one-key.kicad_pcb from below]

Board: 2 copper layers, 14.5 x 14.5 mm, 10 parts (10 on the bottom side), 16 nets.

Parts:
C1, C3: 0.1uF; C_0402_NoSilk
C2, C4: 4.7uF; C_0402_NoSilk
J1: USB_OTG; USB_Micro_NoSlots_NoSilk
J2, J3, J4: Conn_01x04; Pin_Header_Angled_1x04_Pitch1.27mm_no_silk_castellated
SW1: SW_Push; Cherry_MX_Matias_No_Silk_Border
U1: EFM8UB1_QFN20; QFN20_silabs

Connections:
+3V3: C3.1, C4.1, U1.6
+5V: C1.1, C2.1, J1.1, J2.1, U1.7, U1.8
/C2CK: J2.3, U1.9
/C2D: J2.2, U1.10
/D+: J1.3, U1.4
/D-: J1.2, U1.5
/P0.0: J3.4, U1.2
/P0.1: J3.3, U1.1
/P0.2: J3.2, U1.20
/P0.3: J3.1, U1.19
/P0.4: J4.4, U1.18
/P0.5: J4.3, U1.17
/P0.6: J4.2, U1.16
/P0.7: J4.1, U1.15
GND: C1.2, C2.2, C3.2, C4.2, J1.5, J2.4, SW1.2, U1.3, U1.12, U1.21
unnamed: SW1.1, U1.11

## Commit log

2017-09-16 init commit
2017-09-16 vbus sense pin needs to be connected
2017-09-16 add keyplus mini schematic
2017-09-17 add mechanical information for keyplus mini
2017-09-17 add basic wiring information
2017-09-17 add link to firmware loader realeases
2017-09-17 add hardware files
2017-09-17 add images and license text
2017-09-17 add images to readmes
2017-09-17 move readme to base directory
2017-09-17 add missing BOM
2017-09-20 fix some typos
2017-09-20 add notes about unifying receivers
2017-09-20 add note about configuring RF receivers
2017-12-03 add new split 40 percent
2017-12-03 fix descriptions in readme's
2017-12-05 astron usb-c connector
2017-12-05 add μ-board, pro-micro like xmega board
2017-12-05 clean up libraries
2017-12-05 cleanup keyplus mini_v3
2017-12-05 fix typo in readme
2017-12-10 minor PCB fixes and BOM updates
2017-12-10 use slots in mx footprint to appease PCB fab
2017-12-10 one mounting hole not aligned properly
2017-12-12 reposition mounting holes
2017-12-28 updates for alpha split based on v2 prototype board
2017-12-31 BAT_PROG signal not connected properly
2018-01-03 add Tag Connect programming header
2018-01-09 add ghost pcb
2018-01-10 give up on trying to support multiple switch layouts
2018-01-10 rename alpha split to gamma split
2018-01-10 fix bad USB-C connector library
2018-01-10 remove bad library
2018-01-10 remove soldermask around cr2032 battery contact
2018-01-11 add spectre
2018-01-13 add some alternative xmegas
2018-03-10 add kailh low profile
2018-03-25 update keyplus mini files for v3
2018-03-25 update spectre BOM and move USB C port out farther
2018-03-25 update spectre image
2018-03-28 add schematic for rev 3
2018-04-19 add keyplus_mini_v3 kicad footprints
2018-04-19 start experimenting with 2key efm8

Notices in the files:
gamma_split/gamma_split.kicad_pcb:
©jem@seethis.link
keyplus_mini/keyplus_mini_v3/keyplus_mini.kicad_pcb:
©jem
